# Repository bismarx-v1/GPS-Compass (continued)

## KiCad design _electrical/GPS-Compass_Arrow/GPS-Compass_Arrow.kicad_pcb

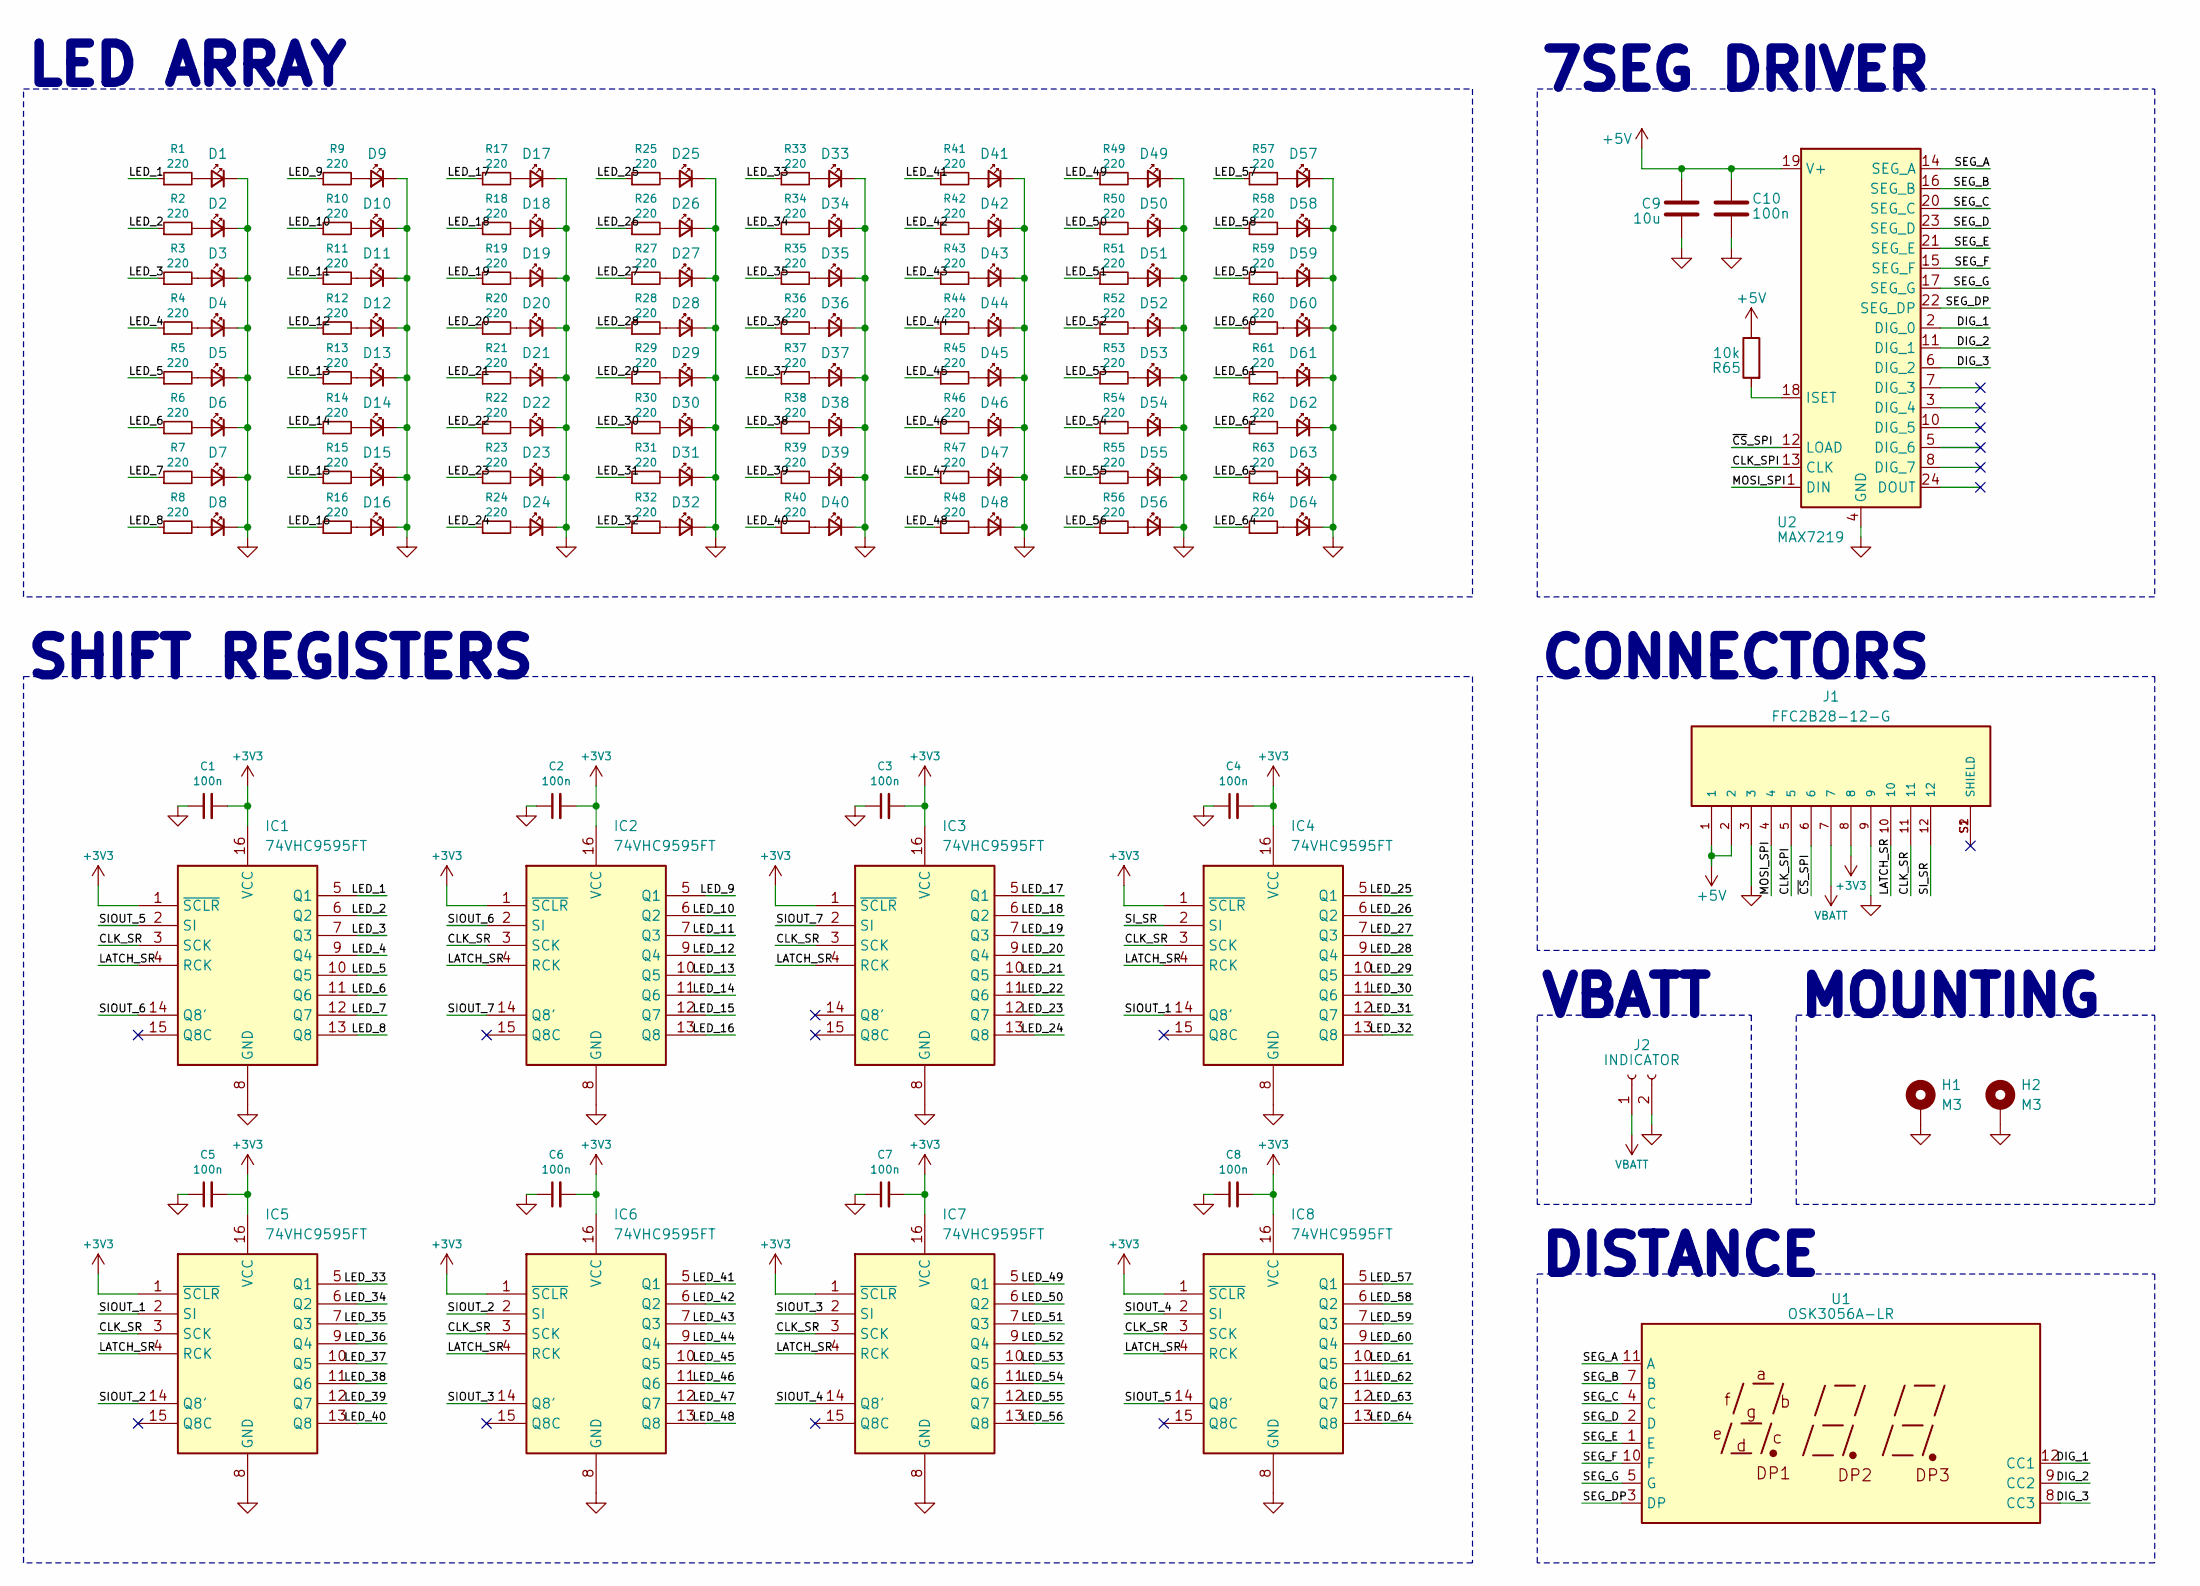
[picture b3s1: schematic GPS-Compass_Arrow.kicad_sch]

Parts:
C1, C2, C3, C4, C5, C6, C7, C8, C10: 100n; C_0805_2012Metric
C9: 10u; C_0805_2012Metric
D1, D2, D3, D4, D5, D6, D7, D8, D9, D10, D11, D12, D13, D14, D15, D16, D17, D18, D19, D20, D21, D22, D23, D24, D25, D26, D27, D28, D29, D30, D31, D32, D33, D34, D35, D36, D37, D38, D39, D40, D41, D42, D43, D44, D45, D46, D47, D48, D49, D50, D51, D52, D53, D54, D55, D56, D57, D58, D59, D60, D61, D62, D63, D64: LED_Small; LED_0603_1608Metric
H1, H2: M3; MountingHole_3.2mm_M3_Pad_Via
IC1, IC2, IC3, IC4, IC5, IC6, IC7, IC8: 74VHC9595FT; SOP65P640X120-16N; Mouser Part Number 757-74VHC9595FT
J1: FFC2B28-12-G; GCT_FFC2B28-12-G; PARTREV A
J2: INDICATOR; PinHeader_1x02_P2.54mm_Vertical
R1, R2, R3, R4, R5, R6, R7, R8, R9, R10, R11, R12, R13, R14, R15, R16, R17, R18, R19, R20, R21, R22, R23, R24, R25, R26, R27, R28, R29, R30, R31, R32, R33, R34, R35, R36, R37, R38, R39, R40, R41, R42, R43, R44, R45, R46, R47, R48, R49, R50, R51, R52, R53, R54, R55, R56, R57, R58, R59, R60, R61, R62, R63, R64: 220; R_0603_1608Metric
R65: 10k; R_0805_2012Metric
U1: OSK3056A-LR
U2: MAX7219; SOP-24_7.5x15.4mm_P1.27mm

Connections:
+3V3: C1.2, C2.2, C3.2, C4.2, C5.2, C6.2, C7.2, C8.2, IC1.1 (~SCLR), IC1.16 (VCC), IC2.1 (~SCLR), IC2.16 (VCC), IC3.1 (~SCLR), IC3.16 (VCC), IC4.1 (~SCLR), IC4.16 (VCC), IC5.1 (~SCLR), IC5.16 (VCC), IC6.1 (~SCLR), IC6.16 (VCC), IC7.1 (~SCLR), IC7.16 (VCC), IC8.1 (~SCLR), IC8.16 (VCC), J1.8
+5V: C9.2, C10.2, J1.1, J1.2, R65.1, U2.19 (V+)
/CLK_SPI: J1.5, U2.13 (CLK)
/CLK_SR: IC1.3 (SCK), IC2.3 (SCK), IC3.3 (SCK), IC4.3 (SCK), IC5.3 (SCK), IC6.3 (SCK), IC7.3 (SCK), IC8.3 (SCK), J1.11
/DIG_1: U1.12 (CC1), U2.2 (DIG_0)
/DIG_2: U1.9 (CC2), U2.11 (DIG_1)
/DIG_3: U1.8 (CC3), U2.6 (DIG_2)
/LATCH_SR: IC1.4 (RCK), IC2.4 (RCK), IC3.4 (RCK), IC4.4 (RCK), IC5.4 (RCK), IC6.4 (RCK), IC7.4 (RCK), IC8.4 (RCK), J1.10
/LED_1: IC1.5 (Q1), R1.1
/LED_2: IC1.6 (Q2), R2.1
/LED_3: IC1.7 (Q3), R3.1
/LED_4: IC1.9 (Q4), R4.1
/LED_5: IC1.10 (Q5), R5.1
/LED_6: IC1.11 (Q6), R6.1
/LED_7: IC1.12 (Q7), R7.1
/LED_8: IC1.13 (Q8), R8.1
/LED_9: IC2.5 (Q1), R9.1
/LED_10: IC2.6 (Q2), R10.1
/LED_11: IC2.7 (Q3), R11.1
/LED_12: IC2.9 (Q4), R12.1
/LED_13: IC2.10 (Q5), R13.1
/LED_14: IC2.11 (Q6), R14.1
/LED_15: IC2.12 (Q7), R15.1
/LED_16: IC2.13 (Q8), R16.1
/LED_17: IC3.5 (Q1), R17.1
/LED_18: IC3.6 (Q2), R18.1
/LED_19: IC3.7 (Q3), R19.1
/LED_20: IC3.9 (Q4), R20.1
/LED_21: IC3.10 (Q5), R21.1
/LED_22: IC3.11 (Q6), R22.1
/LED_23: IC3.12 (Q7), R23.1
/LED_24: IC3.13 (Q8), R24.1
/LED_25: IC4.5 (Q1), R25.1
/LED_26: IC4.6 (Q2), R26.1
/LED_27: IC4.7 (Q3), R27.1
/LED_28: IC4.9 (Q4), R28.1
/LED_29: IC4.10 (Q5), R29.1
/LED_30: IC4.11 (Q6), R30.1
/LED_31: IC4.12 (Q7), R31.1
/LED_32: IC4.13 (Q8), R32.1
/LED_33: IC5.5 (Q1), R33.1
/LED_34: IC5.6 (Q2), R34.1
/LED_35: IC5.7 (Q3), R35.1
/LED_36: IC5.9 (Q4), R36.1
/LED_37: IC5.10 (Q5), R37.1
/LED_38: IC5.11 (Q6), R38.1
/LED_39: IC5.12 (Q7), R39.1
/LED_40: IC5.13 (Q8), R40.1
/LED_41: IC6.5 (Q1), R41.1
/LED_42: IC6.6 (Q2), R42.1
/LED_43: IC6.7 (Q3), R43.1
/LED_44: IC6.9 (Q4), R44.1
/LED_45: IC6.10 (Q5), R45.1
/LED_46: IC6.11 (Q6), R46.1
/LED_47: IC6.12 (Q7), R47.1
/LED_48: IC6.13 (Q8), R48.1
/LED_49: IC7.5 (Q1), R49.1
/LED_50: IC7.6 (Q2), R50.1
/LED_51: IC7.7 (Q3), R51.1
/LED_52: IC7.9 (Q4), R52.1
/LED_53: IC7.10 (Q5), R53.1
/LED_54: IC7.11 (Q6), R54.1
/LED_55: IC7.12 (Q7), R55.1
/LED_56: IC7.13 (Q8), R56.1
/LED_57: IC8.5 (Q1), R57.1
/LED_58: IC8.6 (Q2), R58.1
/LED_59: IC8.7 (Q3), R59.1
/LED_60: IC8.9 (Q4), R60.1
/LED_61: IC8.10 (Q5), R61.1
/LED_62: IC8.11 (Q6), R62.1
/LED_63: IC8.12 (Q7), R63.1
/LED_64: IC8.13 (Q8), R64.1
/MOSI_SPI: J1.4, U2.1 (DIN)
/SEG_A: U1.11 (A), U2.14 (SEG_A)
/SEG_B: U1.7 (B), U2.16 (SEG_B)
/SEG_C: U1.4 (C), U2.20 (SEG_C)
/SEG_D: U1.2 (D), U2.23 (SEG_D)
/SEG_DP: U1.3 (DP), U2.22 (SEG_DP)
/SEG_E: U1.1 (E), U2.21 (SEG_E)
/SEG_F: U1.10 (F), U2.15 (SEG_F)
/SEG_G: U1.5 (G), U2.17 (SEG_G)
/SIOUT_1: IC4.14 (Q8'), IC5.2 (SI)
/SIOUT_2: IC5.14 (Q8'), IC6.2 (SI)
/SIOUT_3: IC6.14 (Q8'), IC7.2 (SI)
/SIOUT_4: IC7.14 (Q8'), IC8.2 (SI)
/SIOUT_5: IC1.2 (SI), IC8.14 (Q8')
/SIOUT_6: IC1.14 (Q8'), IC2.2 (SI)
/SIOUT_7: IC2.14 (Q8'), IC3.2 (SI)
/SI_SR: IC4.2 (SI), J1.12
/~CS_SPI: J1.6, U2.12 (LOAD)
GND: C1.1, C2.1, C3.1, C4.1, C5.1, C6.1, C7.1, C8.1, C9.1, C10.1, D1.1 (K), D2.1 (K), D3.1 (K), D4.1 (K), D5.1 (K), D6.1 (K), D7.1 (K), D8.1 (K), D9.1 (K), D10.1 (K), D11.1 (K), D12.1 (K), D13.1 (K), D14.1 (K), D15.1 (K), D16.1 (K), D17.1 (K), D18.1 (K), D19.1 (K), D20.1 (K), D21.1 (K), D22.1 (K), D23.1 (K), D24.1 (K), D25.1 (K), D26.1 (K), D27.1 (K), D28.1 (K), D29.1 (K), D30.1 (K), D31.1 (K), D32.1 (K), D33.1 (K), D34.1 (K), D35.1 (K), D36.1 (K), D37.1 (K), D38.1 (K), D39.1 (K), D40.1 (K), D41.1 (K), D42.1 (K), D43.1 (K), D44.1 (K), D45.1 (K), D46.1 (K), D47.1 (K), D48.1 (K), D49.1 (K), D50.1 (K), D51.1 (K), D52.1 (K), D53.1 (K), D54.1 (K), D55.1 (K), D56.1 (K), D57.1 (K), D58.1 (K), D59.1 (K), D60.1 (K), D61.1 (K), D62.1 (K), D63.1 (K), D64.1 (K), H1.1, H2.1, IC1.8 (GND), IC2.8 (GND), IC3.8 (GND), IC4.8 (GND), IC5.8 (GND), IC6.8 (GND), IC7.8 (GND), IC8.8 (GND), J1.3, J1.9, J2.2, U2.4 (GND), U2.9 (GND)
unnamed: D1.2 (A), R1.2
unnamed: D2.2 (A), R2.2
unnamed: D3.2 (A), R3.2
unnamed: D4.2 (A), R4.2
unnamed: D5.2 (A), R5.2
unnamed: D6.2 (A), R6.2
unnamed: D7.2 (A), R7.2
unnamed: D8.2 (A), R8.2
unnamed: D9.2 (A), R9.2
unnamed: D10.2 (A), R10.2
unnamed: D11.2 (A), R11.2
unnamed: D12.2 (A), R12.2
unnamed: D13.2 (A), R13.2
unnamed: D14.2 (A), R14.2
unnamed: D15.2 (A), R15.2
unnamed: D16.2 (A), R16.2
unnamed: D17.2 (A), R17.2
unnamed: D18.2 (A), R18.2
unnamed: D19.2 (A), R19.2
unnamed: D20.2 (A), R20.2
unnamed: D21.2 (A), R21.2
unnamed: D22.2 (A), R22.2
unnamed: D23.2 (A), R23.2
unnamed: D24.2 (A), R24.2
unnamed: D25.2 (A), R25.2
unnamed: D26.2 (A), R26.2
unnamed: D27.2 (A), R27.2
unnamed: D28.2 (A), R28.2
unnamed: D29.2 (A), R29.2
unnamed: D30.2 (A), R30.2
unnamed: D31.2 (A), R31.2
unnamed: D32.2 (A), R32.2
unnamed: D33.2 (A), R33.2
unnamed: D34.2 (A), R34.2
unnamed: D35.2 (A), R35.2
unnamed: D36.2 (A), R36.2
unnamed: D37.2 (A), R37.2
unnamed: D38.2 (A), R38.2
unnamed: D39.2 (A), R39.2
unnamed: D40.2 (A), R40.2
unnamed: D41.2 (A), R41.2
unnamed: D42.2 (A), R42.2
unnamed: D43.2 (A), R43.2
unnamed: D44.2 (A), R44.2
unnamed: D45.2 (A), R45.2
unnamed: D46.2 (A), R46.2
unnamed: D47.2 (A), R47.2
unnamed: D48.2 (A), R48.2
unnamed: D49.2 (A), R49.2
unnamed: D50.2 (A), R50.2
unnamed: D51.2 (A), R51.2
unnamed: D52.2 (A), R52.2
unnamed: D53.2 (A), R53.2
unnamed: D54.2 (A), R54.2
unnamed: D55.2 (A), R55.2
unnamed: D56.2 (A), R56.2
unnamed: D57.2 (A), R57.2
unnamed: D58.2 (A), R58.2
unnamed: D59.2 (A), R59.2
unnamed: D60.2 (A), R60.2
unnamed: D61.2 (A), R61.2
unnamed: D62.2 (A), R62.2
unnamed: D63.2 (A), R63.2
unnamed: D64.2 (A), R64.2
unnamed: R65.2, U2.18 (ISET)
VBATT: J1.7, J2.1

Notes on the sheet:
7SEG DRIVER
SHIFT REGISTERS
MOUNTING
LED ARRAY
VBATT
CONNECTORS
DISTANCE

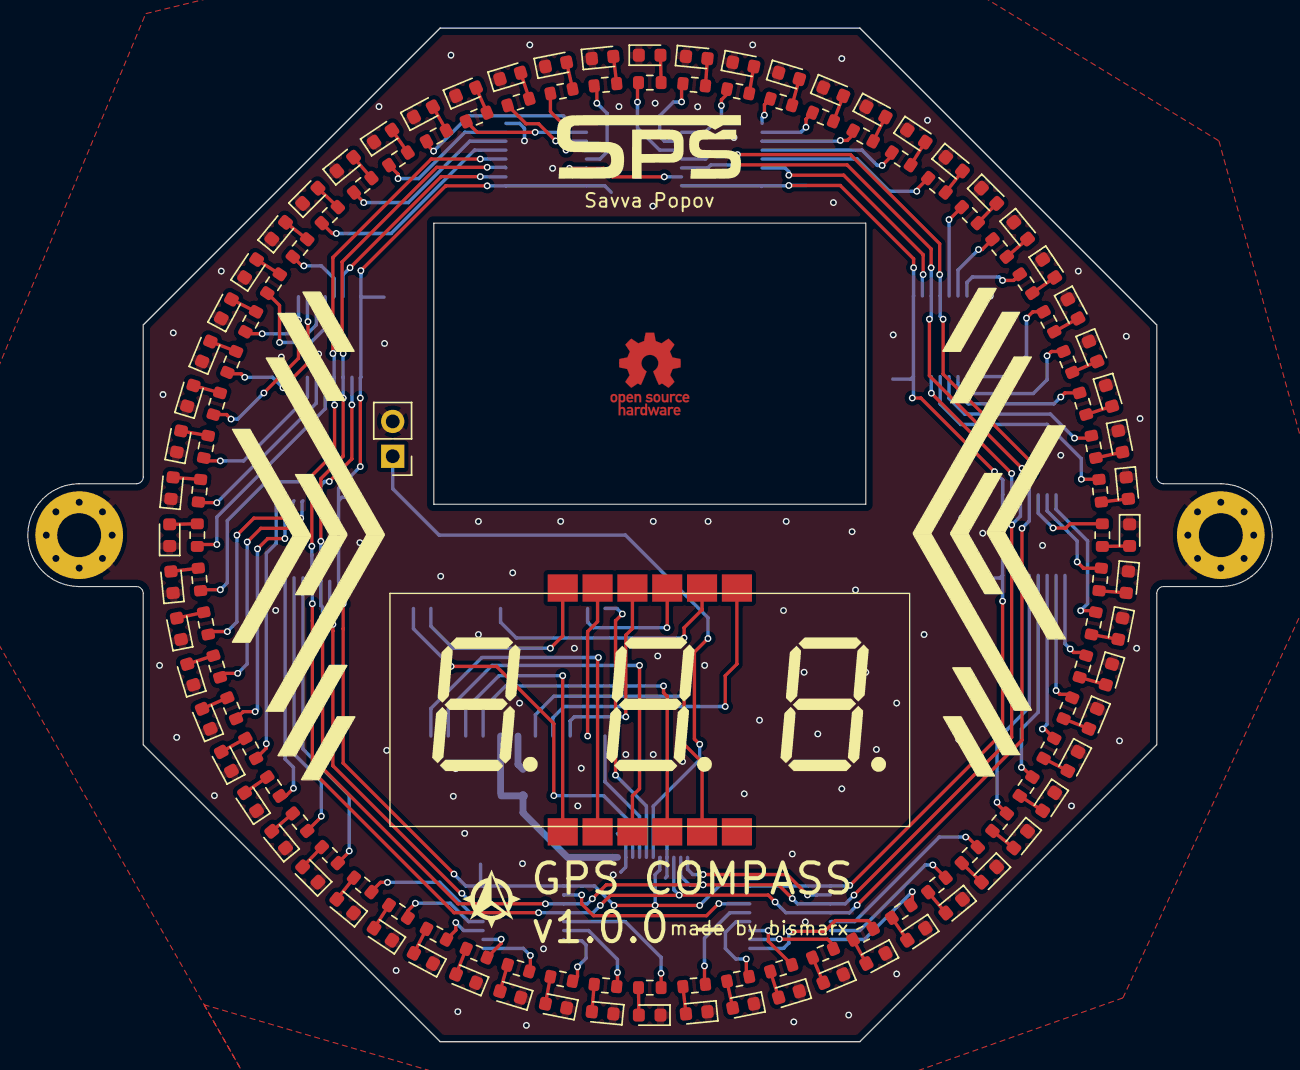
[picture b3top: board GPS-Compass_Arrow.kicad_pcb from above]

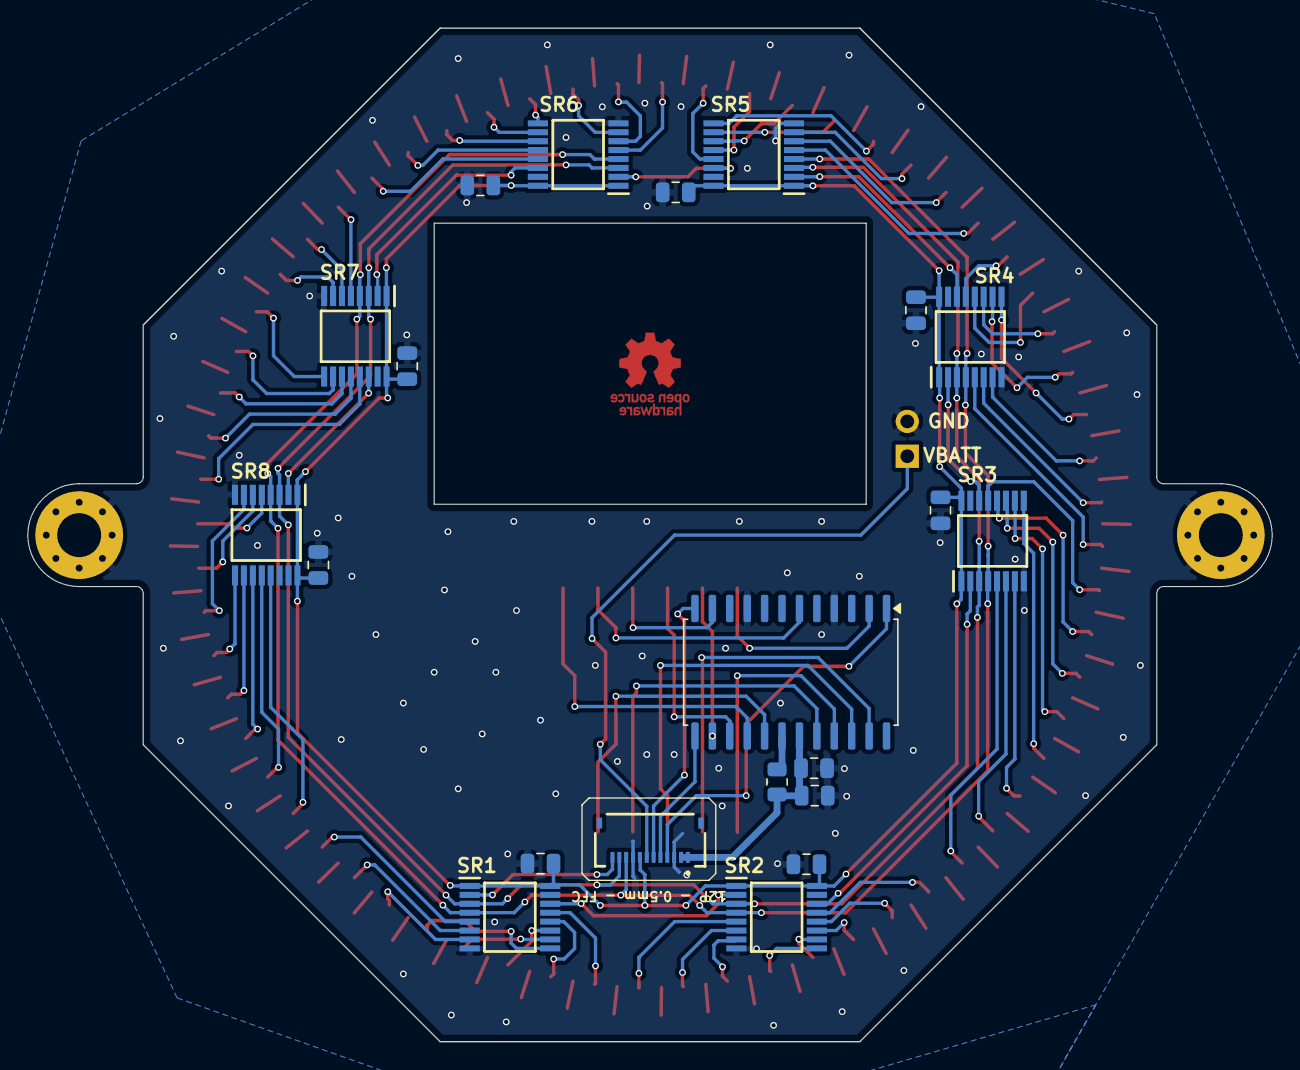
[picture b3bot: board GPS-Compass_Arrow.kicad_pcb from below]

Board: 2 copper layers, 90.8 x 73.9 mm, 153 parts (21 on the bottom side), 157 nets.

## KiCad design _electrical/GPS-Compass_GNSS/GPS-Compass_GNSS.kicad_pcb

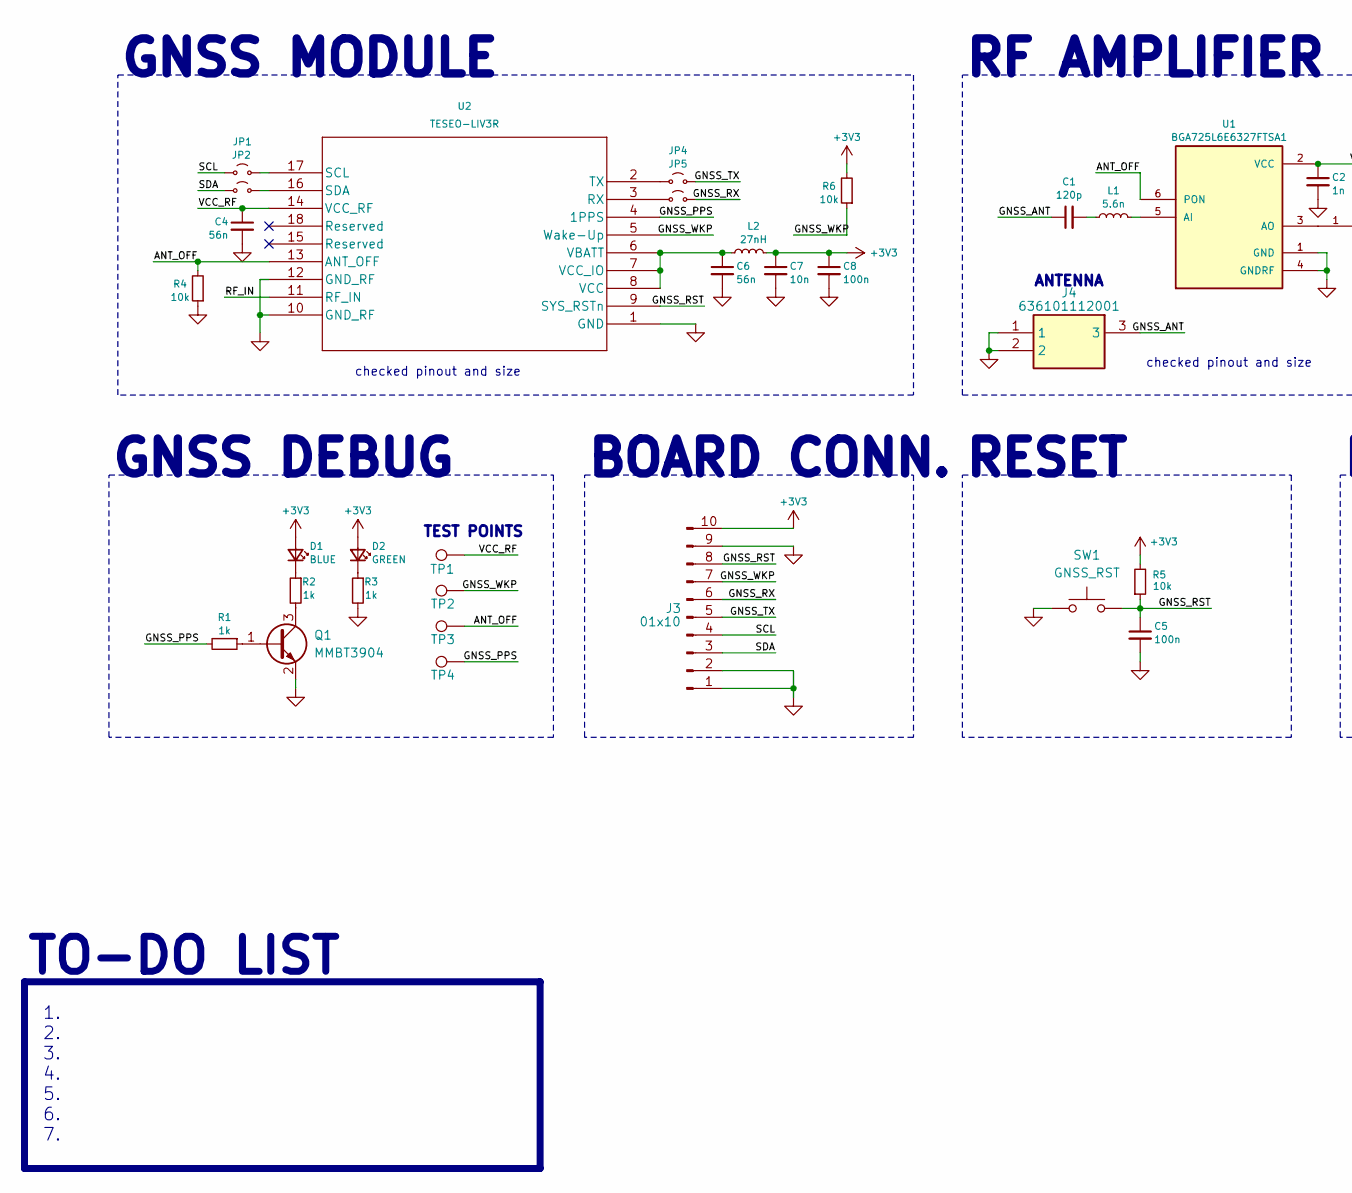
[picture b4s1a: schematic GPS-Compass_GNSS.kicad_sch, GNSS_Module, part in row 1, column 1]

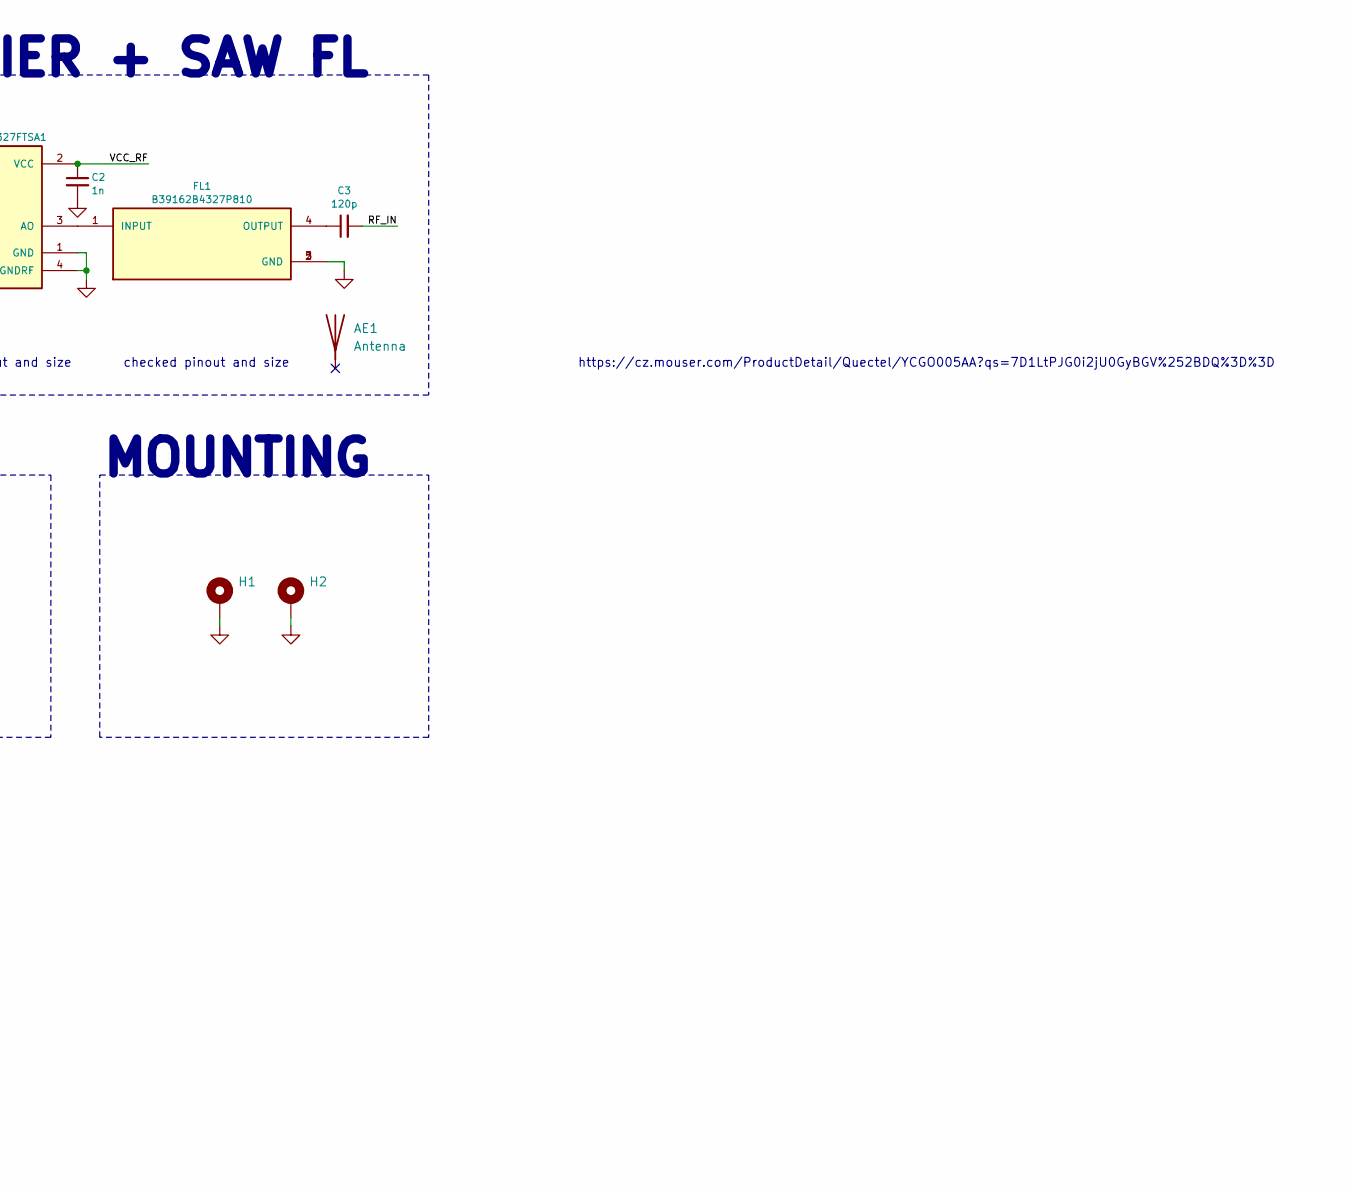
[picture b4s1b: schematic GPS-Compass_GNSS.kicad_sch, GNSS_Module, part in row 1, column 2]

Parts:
AE1: Antenna
C1, C3: 120p; C_0402_1005Metric
C2: 1n; C_0402_1005Metric
C4, C6: 56n; C_0402_1005Metric
C5, C8: 100n; C_0805_2012Metric
C7: 10n; C_0402_1005Metric
D1: BLUE; LED_0805_2012Metric
D2: GREEN; LED_0805_2012Metric
FL1: B39162B4327P810; FIL_B39162B4327P810; PARTREV October 25, 2019
H1, H2: MountingHole_Pad; MountingHole_3.2mm_M3
J3: 01x10; PinHeader_1x10_P2.54mm_Horizontal
J4: 636101112001; Mouser Part Number 710-636101112001
JP1, JP2, JP4, JP5: Jumper_2_Small_Open; SolderJumper-2_P1.3mm_Open_RoundedPad1.0x1.5mm
L1: 5.6n; L_0402_1005Metric
L2: 27nH; L_0402_1005Metric
Q1: MMBT3904; SOT-23
R1, R2, R3: 1k; R_0805_2012Metric
R4: 10k; R_0402_1005Metric
R5, R6: 10k; R_0805_2012Metric
SW1: GNSS_RST; SW_SPST_B3U-1000P
TP1, TP2, TP3, TP4: TestPoint; TestPoint_Pad_D1.0mm
U1: BGA725L6E6327FTSA1; AMP_BGA725L6E6327FTSA1; PARTREV 2.0
U2: TESEO-LIV3R; ARRAY_LIV3R_STM

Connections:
+3V3: C7.1, C8.1, D1.2 (A), D2.2 (A), J3.10, L2.1, R5.2, R6.2
/ANT_OFF: R4.2, TP3.1, U1.6 (PON), U2.13 (ANT_OFF)
/GNSS_ANT: C1.1, J4.3
/GNSS_PPS: R1.2, TP4.1, U2.4 (1PPS)
/GNSS_RST: C5.1, J3.8, R5.1, SW1.2, U2.9 (SYS_RSTn)
/GNSS_RX: J3.6, JP5.1 (A)
/GNSS_TX: J3.5, JP4.1 (A)
/GNSS_WKP: J3.7, R6.1, TP2.1, U2.5 (Wake-Up)
/RF_IN: C3.2, U2.11 (RF_IN)
/SCL: J3.4, JP1.2 (B)
/SDA: J3.3, JP2.2 (B)
/VCC_RF: C2.1, C4.1, TP1.1, U1.2 (VCC), U2.14 (VCC_RF)
GND: C2.2, C4.2, C5.2, C6.2, C7.2, C8.2, FL1.2 (GND), FL1.3 (GND), FL1.5 (GND), H1.1, H2.1, J3.1, J3.2, J3.9, J4.1, J4.2, Q1.2 (E), R3.2, R4.1, SW1.1, U1.1 (GND), U1.4 (GNDRF), U2.1 (GND), U2.10 (GND_RF), U2.12 (GND_RF)
unnamed: C1.2, L1.1
unnamed: D1.1 (K), R2.1
unnamed: D2.1 (K), R3.1
unnamed: FL1.1 (INPUT), U1.3 (AO)
unnamed: C3.1, FL1.4 (OUTPUT)
unnamed: JP1.1 (A), U2.17 (SCL)
unnamed: JP2.1 (A), U2.16 (SDA)
unnamed: JP4.2 (B), U2.2 (TX)
unnamed: JP5.2 (B), U2.3 (RX)
unnamed: Q1.1 (B), R1.1
unnamed: Q1.3 (C), R2.2
unnamed: L1.2, U1.5 (AI)
unnamed: C6.1, L2.2, U2.6 (VBATT), U2.7 (VCC_IO), U2.8 (VCC)

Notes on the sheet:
TO-DO LIST
checked pinout and size
GNSS MODULE
TEST POINTS
BOARD CONN.
MOUNTING
RESET
https://cz.mouser.com/ProductDetail/Quectel/YCGO005AA?qs=7D1LtPJG0i2jU0GyBGV%252BDQ%3D%3D
RF AMPLIFIER + SAW FL
GNSS DEBUG
ANTENNA
1. 2. 3. 4. 5. 6. 7.

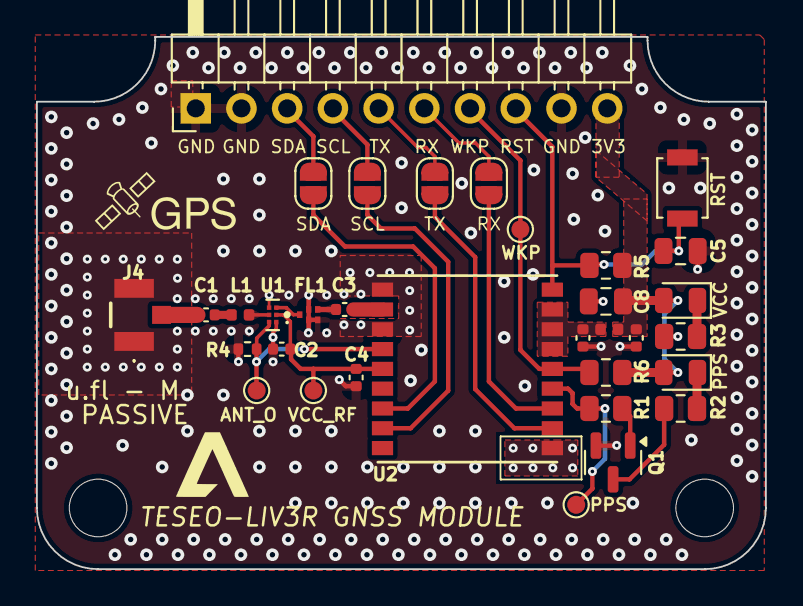
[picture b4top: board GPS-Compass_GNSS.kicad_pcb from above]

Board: 2 copper layers, 40.5 x 29.6 mm, 35 parts (0 on the bottom side), 26 nets.

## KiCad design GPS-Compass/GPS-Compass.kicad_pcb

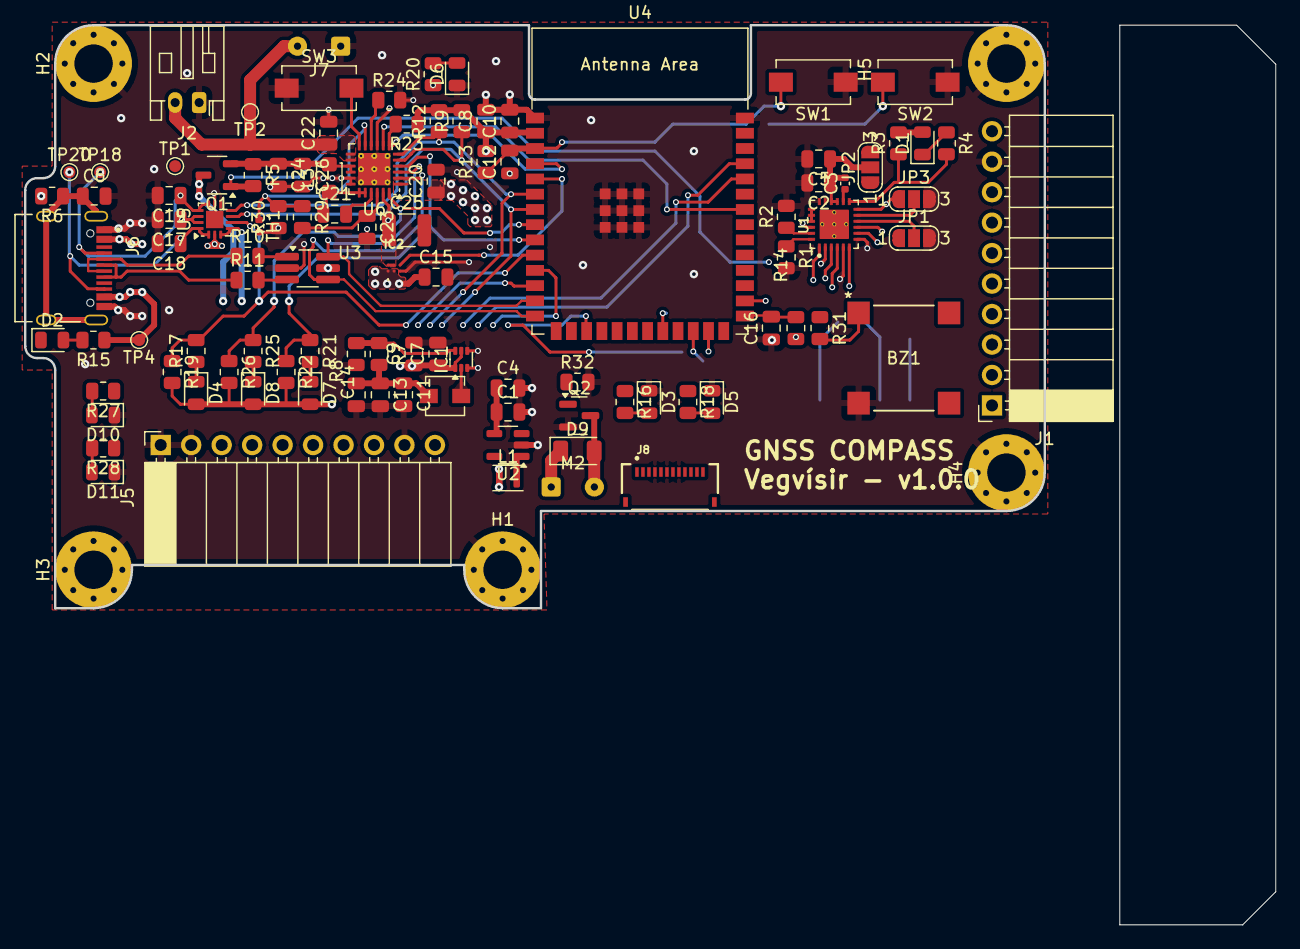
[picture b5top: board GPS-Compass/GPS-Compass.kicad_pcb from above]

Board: 4 copper layers, 85.0 x 48.6 mm, 108 parts (1 on the bottom side), 79 nets.

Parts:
BZ1: Buzzer; AST0827MW-03BTRQ_MAL
C1, C2, C6, C7, C10, C11, C12, C15, C16, C17: 100n; C_0805_2012Metric
C3: 10n; C_0402_1005Metric
C4, C9, C13, C14: 22u; C_0805_2012Metric
C5, C8, C22, C24, C26: 10u; C_0805_2012Metric
C18, C19: 330p; C_0805_2012Metric
C20: 1u; C_0805_2012Metric
C21: 47n; C_0805_2012Metric
C23: 4.7u; C_0805_2012Metric
C25: 47u; C_1210_3225Metric
D1, D2, D3, D4, D5, D6, D7, D8, D10, D11: LED; LED_0805_2012Metric
D9: Schottky; D_1206_3216Metric
H1, H2, H3, H4, H5: Mounting Hole M3; MountingHole_3.2mm_M3_Pad_Via
IC1: TPS565242DRLR; SOT-563
IC2: KTS1605EUB-1-TR; KTS1605EUB1TR
J1: Conn_01x10_Socket; PinSocket_1x10_P2.54mm_Horizontal
J2: Conn_01x02_Pin; JST_PH_S2B-PH-K_1x02_P2.00mm_Horizontal
J3: Motor_conn; JST_XH_S4B-XH-SM4-TB_1x04-1MP_P2.50mm_Horizontal
J5: 01x10; PinSocket_1x10_P2.54mm_Horizontal
J6: USB_TypeC; HRO_TYPE-C-31-M-12
J7: Conn_01x02_Pin; SolderWire-0.1sqmm_1x02_P3.6mm_D0.4mm_OD1mm
J8: FFC2B28-12-G; GCT_FFC2B28-12-G
JP1, JP2, JP3: Jumper; SolderJumper-3_P1.3mm_Open_RoundedPad1.0x1.5mm_NumberLabels
L1: 2,2u; L_Murata_DFE201610P
L2: 1.5u; L_Vishay_IHLP-1212
L3: 2.2uH; L_Walsin_WLFM201609x
M2: Motor_DC; SolderWire-0.1sqmm_1x02_P3.6mm_D0.4mm_OD1mm
Q1: SI2393DS; SOT-23-3
Q2: DMG3406L; SOT-23
R1, R2: R(SET); R_0805_2012Metric
R3, R5, R8, R9, R12, R13, R14, R19, R22, R23, R26, R32: 10k; R_0805_2012Metric
R4, R17: 2.2K; R_0805_2012Metric
R6: 100k; R_0805_2012Metric
R7: 45k; R_0805_2012Metric
R10, R11: 15R; R_0805_2012Metric
R15, R16, R18, R20, R21, R25: 2.2k; R_0805_2012Metric
R24: RLIM; R_0805_2012Metric
R27, R28: 220R; R_0805_2012Metric
R29: 5.23k; R_0805_2012Metric
R30: 30.1k; R_0805_2012Metric
R31: 0R; R_0805_2012Metric
SW1: RESET; SW_SPST_EVQPE1
SW2: BOOT; SW_SPST_EVQPE1
SW3: SHIP-MODE; SW_SPST_EVQPE1
TH1: 10k NTC; R_0402_1005Metric
TP1, TP2, TP4, TP18, TP20: TestPoint; TestPoint_Pad_D1.0mm
U1: DRV8834RGER; DRIVER_DRV8834RGER
U2: TPS613222ADBV; SOT-23-5
U3: USBLC6-2SC6; TSOT-23-6_HandSoldering
U4: ESP32-S3-WROOM-1
U5: FUSB302B11MPX; WQFN-14-1EP_2.5x2.5mm_P0.5mm_EP1.45x1.45mm
U6: BQ25895RTW; Texas_RTW_WQFN-24-1EP_4x4mm_P0.5mm_EP2.7x2.7mm_ThermalVias

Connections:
+3V3: C8.1, C10.1, C11.1, C13.1, C14.1, C17.1, D1.2 (A), D4.2 (A), D7.2 (A), D8.2 (A), D9.1 (K), J1.10, J5.10, JP1.1 (A), JP2.1 (A), JP3.1 (A), L2.2, M2.1 (+), R3.2, R7.2, R9.2, R12.2, R13.2, R14.2, R18.1, R19.2, R22.2, R23.1, R26.2, U1.12 (CONFIG), U1.22 (NSLEEP), U4.2 (3V3), U5.3 (VDD), U5.4 (VDD), U5.12 (VCONN), U5.13 (VCONN)
+5V: C1.1, C4.1, J8.10, J8.11, J8.12, JP2.3 (B), R16.1, U2.4 (VOUT)
/BOOT: C16.2, R14.1, SW2.2, U4.27 (IO0)
/CC1: C19.1, J6.A5 (CC1), TP18.1, U5.10 (CC1), U5.11 (CC1)
/CC2: C18.1, J6.B5 (CC2), TP20.1, U5.1 (CC2), U5.14 (CC2)
/CLK: J8.7, U4.38 (IO2)
/D+: U3.4, U4.14 (IO20), U6.2 (D+)
/D-: U3.6, U4.13 (IO19), U6.3 (D-)
/DBNCD_0: J1.2, U4.29 (IO36)
/DBNCD_1: J1.3, U4.30 (IO37)
/DBNCD_2: J1.6, U4.32 (IO39)
/DBNCD_3: J1.7, U4.33 (IO40)
/DIR: U1.9 (DIR/BPHASE), U4.25 (IO48)
/DN_IN: J6.A7 (DN1), J6.B7 (DN2), R10.1
/DP_IN: J6.A6 (DP1), J6.B6 (DP2), R11.1
/DSEL: R25.1, R26.1, U4.8 (IO15), U6.24 (DSEL)
/EN: C12.2, J1.8, R13.1, SW1.2, U4.3 (EN)
/EN_LS: IC2.C2 (EN), U4.5 (IO5)
/GNSS_RST: J1.1, J5.8, U4.17 (IO9)
/GNSS_RX: J5.6, U4.37 (IO43)
/GNSS_TX: J5.5, U4.36 (IO44)
/GNSS_WKP: J5.7, U4.11 (IO18)
/INT_CHRG: R23.2, U4.4 (IO4), U6.7 (INT)
/INT_UCON: R17.2, R19.1, U4.10 (IO17), U5.5 (INT_N)
/LED_EXT: J1.4, U4.31 (IO38)
/LED_IO13: R28.1, U4.21 (IO13)
/LED_IO21: R27.1, U4.23 (IO21)
/M0: JP1.2 (C), U1.10 (M0/APHASE)
/M1: JP3.2 (C), U1.11 (M1)
/MOSI: J8.9, U4.35 (IO42)
/MSW_ON: J1.5, Q1.1 (G), R5.2
/NFAULT: R3.1, R4.2, U1.13 (NFAULT), U4.28 (IO35)
/OTG: U4.34 (IO41), U6.8 (OTG)
/PWM_BZ: R31.1, U4.12 (IO8)
/PWM_HPTCS: Q2.1 (G), R32.1, U4.22 (IO14)
/SCL: J5.4, R9.1, U4.7 (IO7), U5.6 (SCL), U6.5 (SCL)
/SDA: J5.3, R12.1, U4.6 (IO6), U5.7 (SDA), U6.6 (SDA)
/STAT: R21.1, R22.1, U4.9 (IO16), U6.4 (STAT)
/STEP: U1.8 (STEP/BENBL), U4.24 (IO47)
/TS: R29.1, R30.2, TH1.1, U6.11 (TS)
/~CS: J8.5, U4.39 (IO1)
GND: BZ1.2 (-), C1.2, C2.2, C4.2, C5.2, C6.2, C7.2, C8.2, C9.2, C10.2, C11.2, C12.1, C13.2, C14.2, C15.2, C16.1, C17.2, C18.2, C19.2, C20.2, C22.2, C23.2, C24.2, C25.2, C26.2, D2.1 (K), D3.1 (K), D5.1 (K), D6.1 (K), D10.1 (K), D11.1 (K), H1.1, H2.1, H3.1, H4.1, H5.1, IC1.3 (GND), IC1.4 (AGND), IC2.C1 (GND), J1.9, J2.1, J5.1, J5.2, J5.9, J6.A1_B12 (GND), J6.B1_A12 (GND), J7.1, J8.4, J8.6, J8.8, JP1.3 (B), JP3.3 (B), Q2.2 (S), R1.2, R2.2, R6.2, R8.1, R24.2, R30.1, R32.2, SW1.1, SW2.1, SW3.1, TH1.2, U1.2 (AISEN), U1.5 (BISEN), U1.7 (NENBL/AENBL), U1.18 (GND), U1.25 (GND), U1.25.1 (GND), U1.25.2 (GND), U1.25.3 (GND), U1.25.4 (GND), U1.25.5 (GND), U2.2 (GND), U3.2, U4.1 (GND), U4.40 (GND), U4.41 (GND), U5.8 (GND), U5.9 (GND), U5.15 (GND), U6.9 (~CE), U6.17 (PGND), U6.18 (PGND), U6.25 (PGND)
unnamed: BZ1.1 (+), R31.2
unnamed: C6.1, J6.S1 (SHIELD), J6.S2 (SHIELD), J6.S3 (SHIELD), J6.S4 (SHIELD), R6.1
unnamed: C21.1, L3.1, U6.19 (SW), U6.20 (SW)
unnamed: D1.1 (K), R4.1
unnamed: D2.2 (A), R15.2
unnamed: D3.2 (A), R16.2
unnamed: D4.1 (K), R17.1
unnamed: D5.2 (A), R18.2
unnamed: D6.2 (A), R20.2
unnamed: D7.1 (K), R21.2
unnamed: D8.1 (K), R25.2
unnamed: D9.2 (A), M2.2 (-), Q2.3 (D)
unnamed: D10.2 (A), R27.2
unnamed: D11.2 (A), R28.2
unnamed: IC1.6 (FB), R7.1, R8.2
unnamed: IC1.2 (SW), L2.1
unnamed: J3.1, U1.4 (BOUT2)
unnamed: J3.2, U1.6 (BOUT1)
unnamed: J3.3, U1.3 (AOUT2)
unnamed: J3.4, U1.1 (AOUT1)
unnamed: R10.2, U3.1
unnamed: R11.2, U3.3
unnamed: R1.1, U1.24 (ADECAY)
unnamed: R2.1, U1.23 (BDECAY)
unnamed: C3.1, U1.14 (VCP)
unnamed: L1.2, U2.1 (SW)
unnamed: C21.2, U6.21 (BTST)
unnamed: R24.1, U6.10 (ILIM)
unnamed: SW3.2, U6.12 (~QON)
REGN: C23.1, R29.2, U6.22 (REGN)
USB_VBUS: C15.1, C20.1, IC2.A1 (OUT_1), IC2.B1 (OUT_2), J6.A4_B9 (VBUS), J6.B4_A9 (VBUS), R15.1, TP4.1, U3.5, U5.2 (VBUS), U6.1 (VBUS)
VBATT: C22.1, J2.2, J7.2, TP2.1, U6.13 (BAT), U6.14 (BAT)
VIN: C7.1, C9.1, IC1.1 (VIN), IC1.5 (EN), L1.1, Q1.3 (D)
VM: C2.1, C3.2, C5.1, JP2.2 (C), U1.15 (VM), U1.16 (VM)
VOTG: C25.1, IC2.A2 (IN_1), IC2.B2 (IN_2), R20.1, U6.23 (PMID)
VREFO: U1.19 (AVREF), U1.20 (BVREF), U1.21 (VREFO)
VSYS: C24.1, C26.1, L3.2, Q1.2 (S), R5.1, TP1.1, U6.15 (SYS), U6.16 (SYS)

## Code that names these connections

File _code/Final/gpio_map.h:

#ifndef GPIO_MAP
#define GPIO_MAP

enum GPIO_PINS {
    INT_IMU     = 2,  // IMU interrupt
    OTG         = 4,  // USB On-The-Go
    INT_CHRG    = 5,  // Charger interrupt
    SDA         = 6,  // I2C Data
    SCL         = 7,  // I2C Clock
    GNSS_WKP    = 8,  // GNSS Wake-up
    LED_IO9     = 9,  // User LED
    CS_SPI      = 10, // SPI Chip Select
    MOSI_SPI    = 11, // SPI Master Out Slave In
    CLK_SPI     = 12, // SPI Clock
    LED_IO13    = 13, // User LED
    GNSS_RST    = 14, // GNSS Reset
    DSEL        = 15, // Charger USB d+/d- selection status
    STAT        = 16, // Charge Status, Charging in progress = LED ON,  Charge complete = LED OFF,  Charge fault = LED Blinking
    EN_LS       = 17, // Enable Load Switch
    INT_UCON    = 18, // Interrupt USB Controller
    LATCH_SR    = 21, // Latch Shift Register
    DBNCD_0     = 35, // Debounced Input 0
    DBNCD_1     = 36, // Debounced Input 1
    LED_EXT     = 37, // External LED
    DBNCD_2     = 38, // Debounced Input 2
    SI_SR       = 39, // Shift register serial input
    CLK_SR      = 40, // Shift register clock
    FREE_IO41   = 41, // Free General Purpose IO
    FREE_IO42   = 42, // Free General Purpose IO
    GNSS_RX     = 43, // UART_TX
    GNSS_TX     = 44, // UART_RX
    FREE_IO48   = 48, // Free General Purpose IO
};

#endif

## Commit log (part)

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2025-07-18 Schematic update
2025-07-25 gps upd
2025-07-29 pcb update
2025-07-30 Finished PCB layout on edgecuts
2025-08-05 PRTGN stuff
2025-08-06 Buzzer footprint edit
2025-08-12 footprint for different project
2025-08-17 GNSS layout
2025-08-19 GNSS update
2025-08-21 gnss module
2025-08-24 GNSS and Mian ocb
2025-08-24 soldermask via fencing
2025-08-25 finished
2025-08-26 changed socket to header for breadboard pluggablity
2025-08-28 schematric remake
2025-08-29 schematic remake
2025-08-30 new pcb
2025-09-01 UI layout and routing
2025-09-02 GPS Compass - schematic
2025-09-02 layout updates
2025-09-03 routing
2025-09-09 will be remaking the charger probably
2025-09-10 new IC charger
2025-09-10 new usb charger
2025-09-11 UI changes
2025-09-11 jkolsd
2025-09-12 no chsanges
2025-09-14 asdasd
2025-09-17 ?sd,.fvsd';
2025-09-17 asdas
2025-09-18 im to tired to write this shi
2025-09-19 cannot bother
2025-09-22 i think im depressed again
2025-09-24 sdas
2025-09-26 asda
2025-09-27 changes s
2025-09-28 pcb updates
2025-09-29 UI PCB
2025-10-01 UI board updates
2025-10-03 Path updates
2025-10-08 New 3D model
2025-10-11 To do list updated
2025-10-12 dunnop
2025-10-16 SCHEMATIC
2025-10-19 schematic updaete
2025-10-20 no updates
2025-10-23 i dunno
2025-10-26 jkhigyuj
2025-10-27 arrow pcb update
2025-11-03 arrow pcb
2025-11-05 arrow pcp updates
2025-11-06 arrowpcb update
2025-11-06 main pcb update
2025-11-07 main pcb and arrow updatws
2025-11-09 updates on different boards
2025-11-11 3D model
2025-11-11 folder reloaction
2025-11-11 3d model update
2025-11-12 sadf
2025-11-13 Shift register code
2025-11-17 bpx update and new top part started
2025-11-18 3D updates
2025-11-19 main pcb updates
2025-11-19 generated step files
2025-11-19 3d and PCB
2025-11-20 PCB and 3D updates
2025-11-25 sdfdsf
2025-11-27 new renders and 3d updat4ws
2025-12-01 production updates
2025-12-03 moved
2025-12-03 moved files
2025-12-03 ZSzxc
2025-12-05 BOM update
2025-12-09 stuff
2025-12-09 pls dont break
2025-12-09 new renders
2025-12-11 arrow pcb new desing
2025-12-11 lots of updates
2025-12-13 mechanical
2025-12-14 renders
2025-12-15 sdaawd
2025-12-15 gitignore sdt
2025-12-17 qweq
2025-12-18 jkhbvijyhu
2025-12-20 apiosjd
2025-12-20 cleanup of stuff
2025-12-22 asdasdasdasdasdadassddadasasdasdsdaasdasddasdasdasdasdasas
    asdasdasdasdasdddasasdasdasdadasdadsasdasdasdasasdasddaasdasdasdaasdasdasdasdaasdasdasd
2025-12-25 webserver completed
2025-12-28 Code update
2025-12-30 GPIO map and QR code for the assembly
2026-01-08 renders, code
2026-01-09 af wd
2026-01-13 new code update
2026-01-15 charger config update
2026-01-15 new main code
2026-01-16 remade headers from RNS
2026-01-17 teseo suite
2026-01-17 CODE 3D
2026-01-18 3D update
2026-01-20 3d update
    hopefully final
2026-01-23 code updates
2026-01-25 footperint addded
2026-01-27 new code update from rose
2026-01-31 rose code update
2026-01-31 teseo-liv3r sw manual
2026-02-01 rose code updates
2026-02-02 I2C scanner
2026-02-02 IMU test
2026-02-05 parser
2026-02-15 Code update, schematic plots, text update
2026-02-19 I2C GNSS update
2026-02-19 NMEA update
2026-02-20 IMU visualizer
2026-02-20 IMU viz
2026-02-23 IMU.py
2026-03-01 IMU changed to quaternion
2026-03-01 moved in different folder
2026-03-05 IMU update
2026-03-06 final edits before handing in
2026-03-29 new 3d updates for user manual
2026-04-15 renders, model updates, presentation
2026-04-17 code libs update
2026-05-06 New IMU visualisation code
